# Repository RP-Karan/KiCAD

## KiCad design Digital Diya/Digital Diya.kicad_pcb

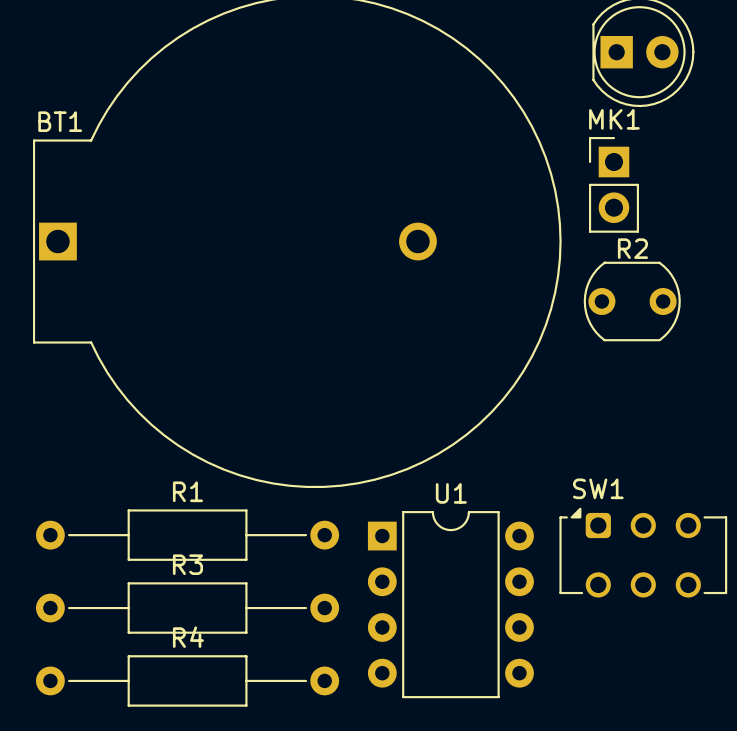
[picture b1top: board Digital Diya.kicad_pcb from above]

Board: 2 copper layers, 9 parts (0 on the bottom side), 7 nets, no tracks yet.

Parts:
BT1: Battery_Cell; BatteryHolder_ComfortableElectronic_CH273-2450_1x2450
D1: LED; LED_D5.0mm
MK1: Microphone_Condenser; PinHeader_1x02_P2.54mm_Vertical
R1: 10k; R_Axial_DIN0207_L6.3mm_D2.5mm_P15.24mm_Horizontal
R2: LDR07; R_LDR_5.1x4.3mm_P3.4mm_Vertical
R3: 480R; R_Axial_DIN0207_L6.3mm_D2.5mm_P15.24mm_Horizontal
R4: 5.6k; R_Axial_DIN0207_L6.3mm_D2.5mm_P15.24mm_Horizontal
SW1: SW_DPDT_x2; SW_CK_JS202011AQN_DPDT_Angled
U1: ATtiny85V-10P; DIP-8_W7.62mm

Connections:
+3.3V: BT1.1 (+), R1.1, R4.1, U1.8 (VCC)
/A: D1.2 (A), U1.6 (PB1)
/B: R1.2, R2.1, U1.7 (PB2)
/C: MK1.2 (+), R4.2, U1.2 (XTAL1/PB3)
GND: MK1.1 (-), R2.2, R3.2, SW1.2 (B), U1.4 (GND)
unnamed: BT1.2 (-), SW1.3 (C)
unnamed: D1.1 (K), R3.1

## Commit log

2025-11-23 New Project
2025-11-24 Updated Design
